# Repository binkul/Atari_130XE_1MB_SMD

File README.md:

# This Atari 130 XE motherboard with 1MB SIMM expansion, internal 
- Atari Basic
- Basic XL
- Basic XE
- Action!
- Mac65
- TTP
# in SMD version

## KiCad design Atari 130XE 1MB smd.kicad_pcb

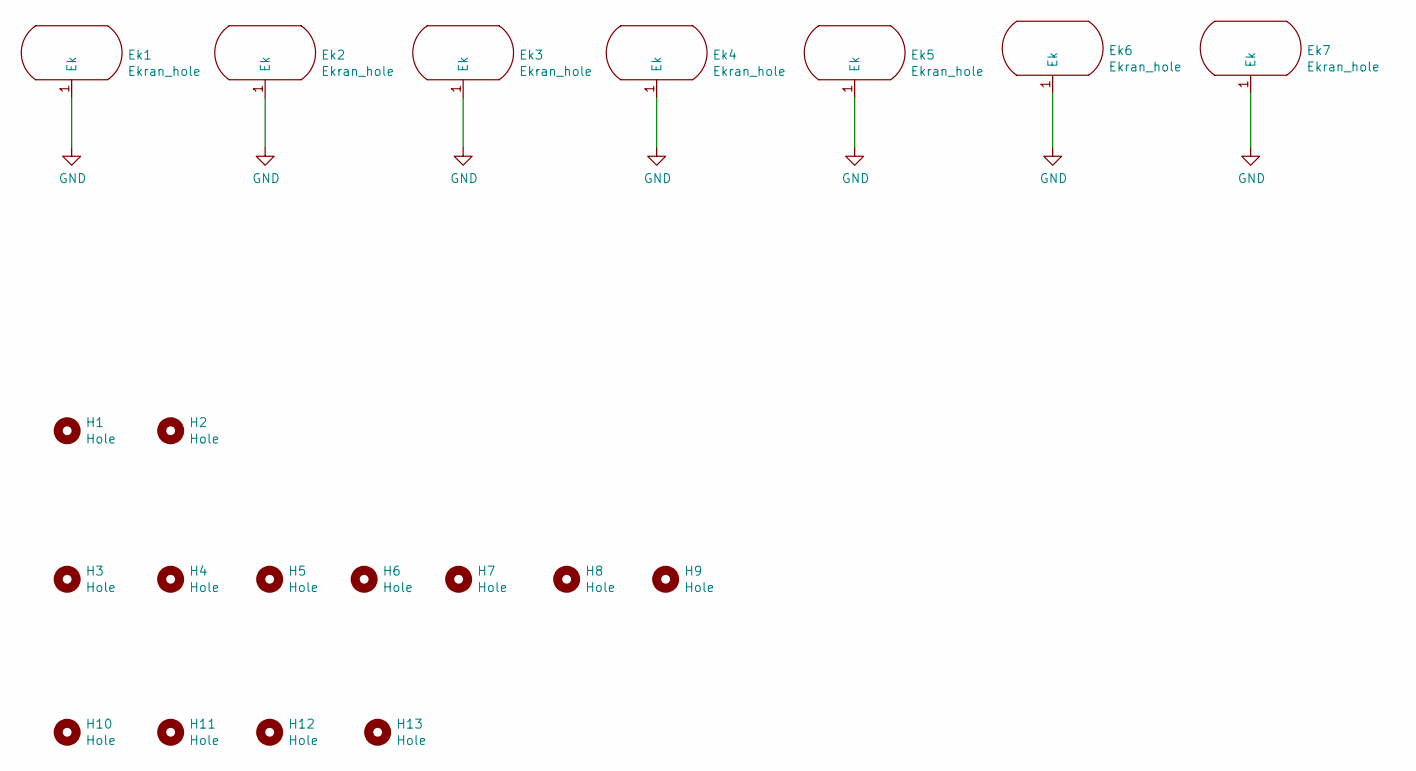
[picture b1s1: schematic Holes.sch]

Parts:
Ek1, Ek2, Ek3, Ek4, Ek5, Ek6, Ek7: Ekran_hole; Ekran_GND
H1, H2: Hole; Medium_hole
H3, H4, H5, H6, H7, H8, H9: Hole; Hole_3.4mm
H10, H11, H12, H13: Hole; Hole_4.4mm

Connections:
GND: Ek1.1, Ek2.1, Ek3.1, Ek4.1, Ek5.1, Ek6.1, Ek7.1; also elsewhere on the board

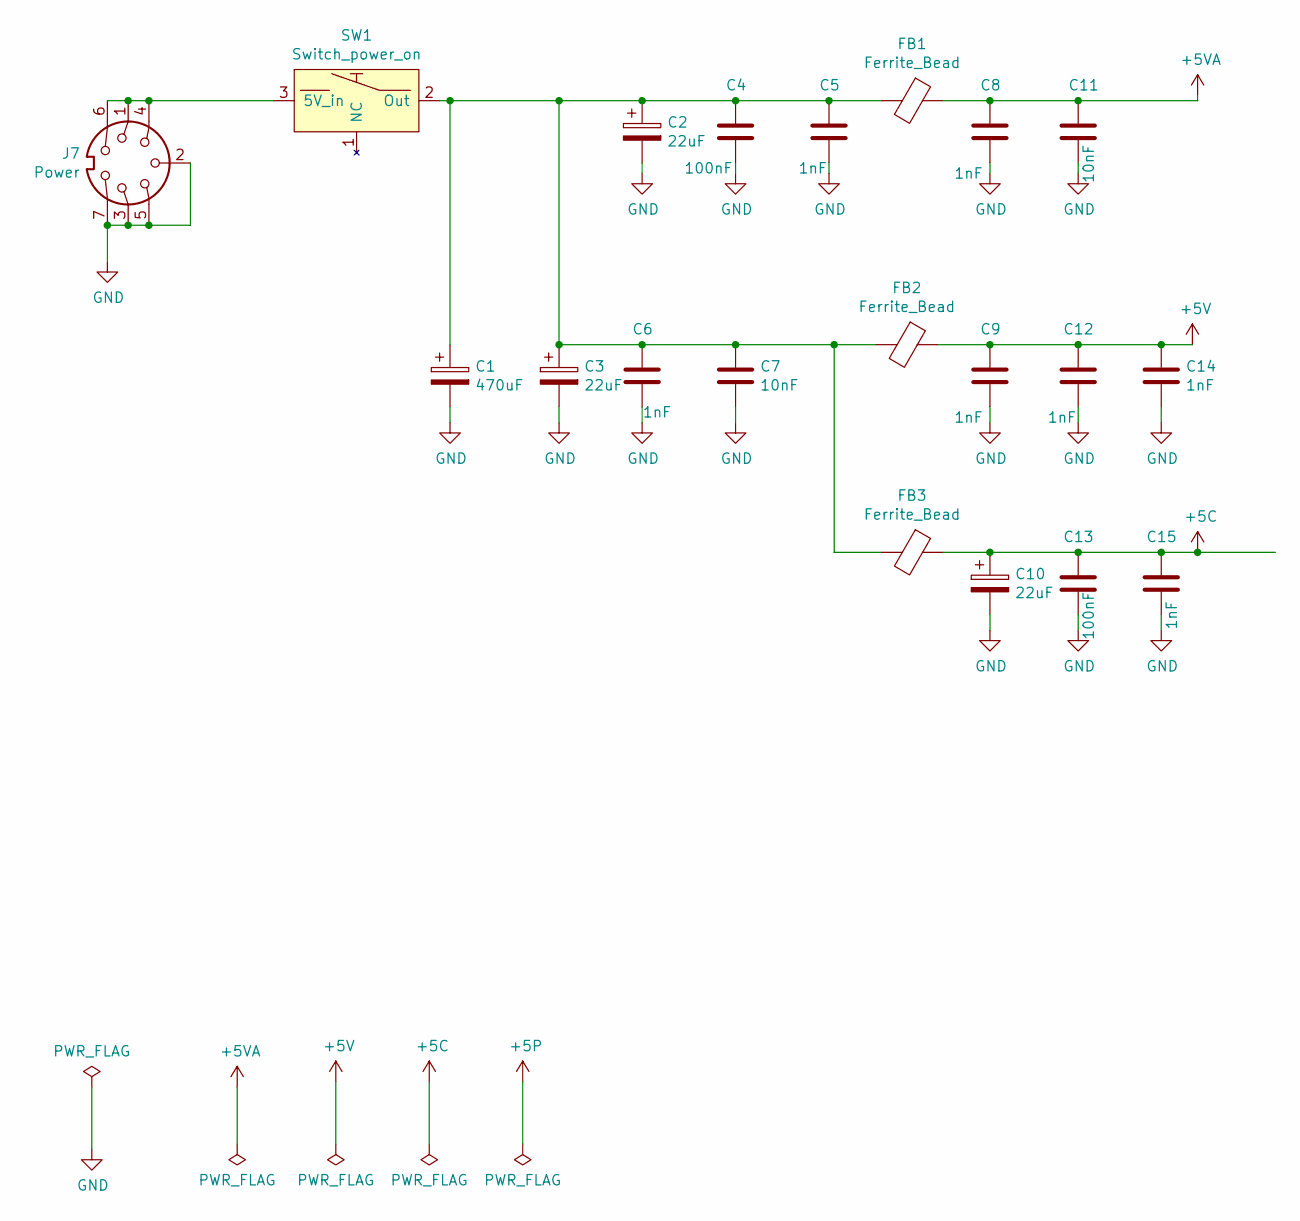
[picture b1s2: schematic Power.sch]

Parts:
C1: 470uF; CP_Elec_10x10.5
C2, C3, C10: 22uF; CP_Elec_6.3x5.2
C4, C13: 100nF; C_1206_3216Metric_Pad1.42x1.75mm_HandSolder
C5, C6, C8, C9, C12, C14, C15: 1nF; C_1206_3216Metric_Pad1.42x1.75mm_HandSolder
C7, C11: 10nF; C_1206_3216Metric_Pad1.42x1.75mm_HandSolder
FB1, FB2, FB3: Ferrite_Bead; L_1812_4532Metric_Pad1.30x3.40mm_HandSolder
J7: Power; DIN_7_pin
SW1: Switch_power_on; Switch_ON-OFF

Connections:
+5C: C10.1, C13.1, C15.1, FB3.1; also elsewhere on the board
+5V: C9.1, C12.1, C14.1, FB2.1
+5VA: C8.1, C11.1, FB1.1; also elsewhere on the board
GND: C1.2, C2.2, C3.2, C4.2, C5.2, C6.2, C7.2, C8.2, C9.2, C10.2, C11.2, C12.2, C13.2, C14.2, C15.2, J7.2, J7.3, J7.5, J7.7; also elsewhere on the board
unnamed: C1.1, C2.1, C3.1, C4.1, C5.1, C6.1, C7.1, FB1.2, FB2.2, FB3.2, SW1.2 (Out)
unnamed: J7.1, J7.4, J7.6, SW1.3 (5V_in)

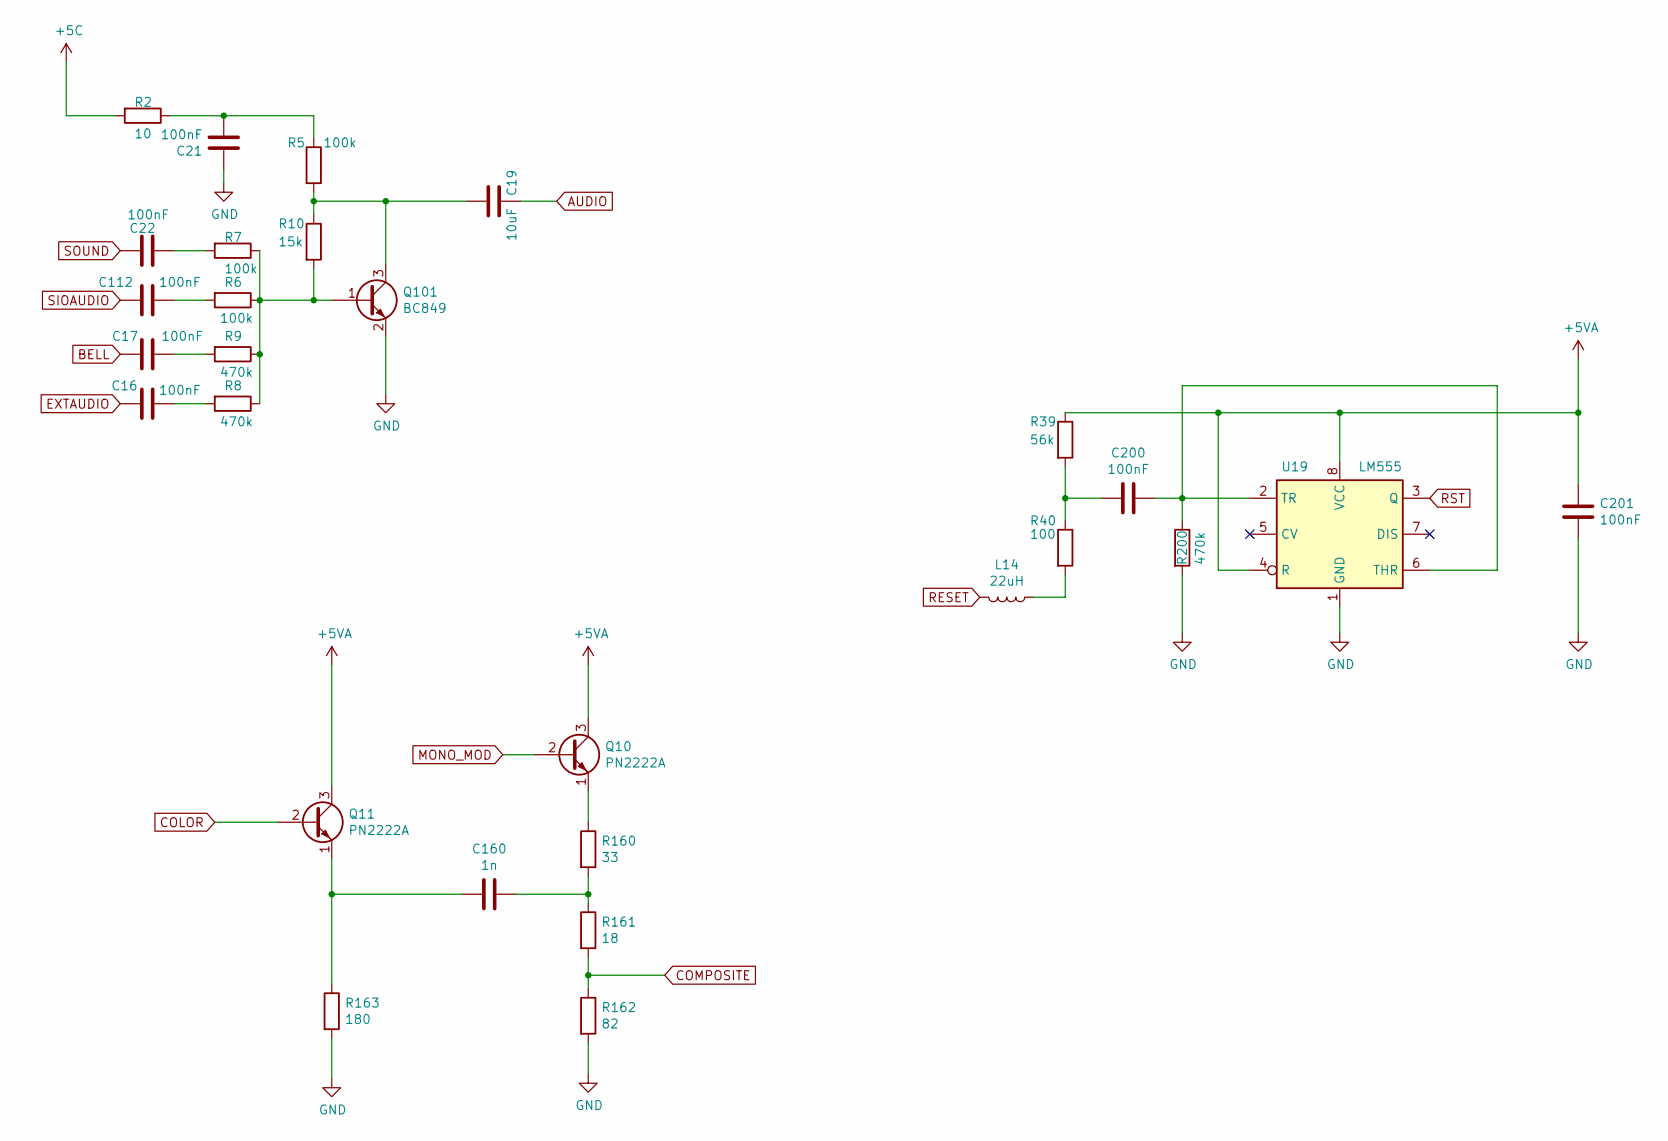
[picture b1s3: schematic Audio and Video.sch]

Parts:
C16, C17, C21, C22, C112, C200, C201: 100nF; C_1206_3216Metric_Pad1.42x1.75mm_HandSolder
C19: 10uF; C_1210_3225Metric_Pad1.42x2.65mm_HandSolder
C160: 1n; C_1206_3216Metric_Pad1.42x1.75mm_HandSolder
L14: 22uH; L_1812_4532Metric_Pad1.30x3.40mm_HandSolder
Q10, Q11: PN2222A; TO-92_Inline
Q101: BC849; SOT-23
R2: 10; R_1206_3216Metric_Pad1.42x1.75mm_HandSolder
R5, R6, R7: 100k; R_1206_3216Metric_Pad1.42x1.75mm_HandSolder
R8, R9, R200: 470k; R_1206_3216Metric_Pad1.42x1.75mm_HandSolder
R10: 15k; R_1206_3216Metric_Pad1.42x1.75mm_HandSolder
R39: 56k; R_1206_3216Metric_Pad1.42x1.75mm_HandSolder
R40: 100; R_1206_3216Metric_Pad1.42x1.75mm_HandSolder
R160: 33; R_1206_3216Metric_Pad1.42x1.75mm_HandSolder
R161: 18; R_1206_3216Metric_Pad1.42x1.75mm_HandSolder
R162: 82; R_1206_3216Metric_Pad1.42x1.75mm_HandSolder
R163: 180; R_1206_3216Metric_Pad1.42x1.75mm_HandSolder
U19: LM555; DIP-8_W7.62mm_Socket

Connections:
+5C: R2.2; also elsewhere on the board
+5VA: C201.1, Q10.3 (C), Q11.3 (C), R39.1, U19.4 (R), U19.8 (VCC); also elsewhere on the board
AUDIO: C19.2; also elsewhere on the board
BELL: C17.2; also elsewhere on the board
COLOR: Q11.2 (B); also elsewhere on the board
COMPOSITE: R161.2, R162.1; also elsewhere on the board
EXTAUDIO: C16.1; also elsewhere on the board
GND: C21.1, C201.2, Q101.2 (E), R162.2, R163.2, R200.2, U19.1 (GND); also elsewhere on the board
MONO_MOD: Q10.2 (B); also elsewhere on the board
unnamed: C16.2, R8.2
unnamed: C17.1, R9.2
unnamed: C19.1, Q101.3 (C), R5.2, R10.1
unnamed: C21.2, R2.1, R5.1
unnamed: C22.2, R7.2
unnamed: C112.2, R6.2
unnamed: C160.1, R160.2, R161.1
unnamed: C160.2, Q11.1 (E), R163.1
unnamed: C200.1, R200.1, U19.2 (TR), U19.6 (THR)
unnamed: C200.2, R39.2, R40.1
unnamed: L14.1, R40.2
unnamed: Q10.1 (E), R160.1
unnamed: Q101.1 (B), R6.1, R7.1, R8.1, R9.1, R10.2
RESET: L14.2; also elsewhere on the board
RST: U19.3 (Q); also elsewhere on the board
SIOAUDIO: C112.1; also elsewhere on the board
SOUND: C22.1; also elsewhere on the board

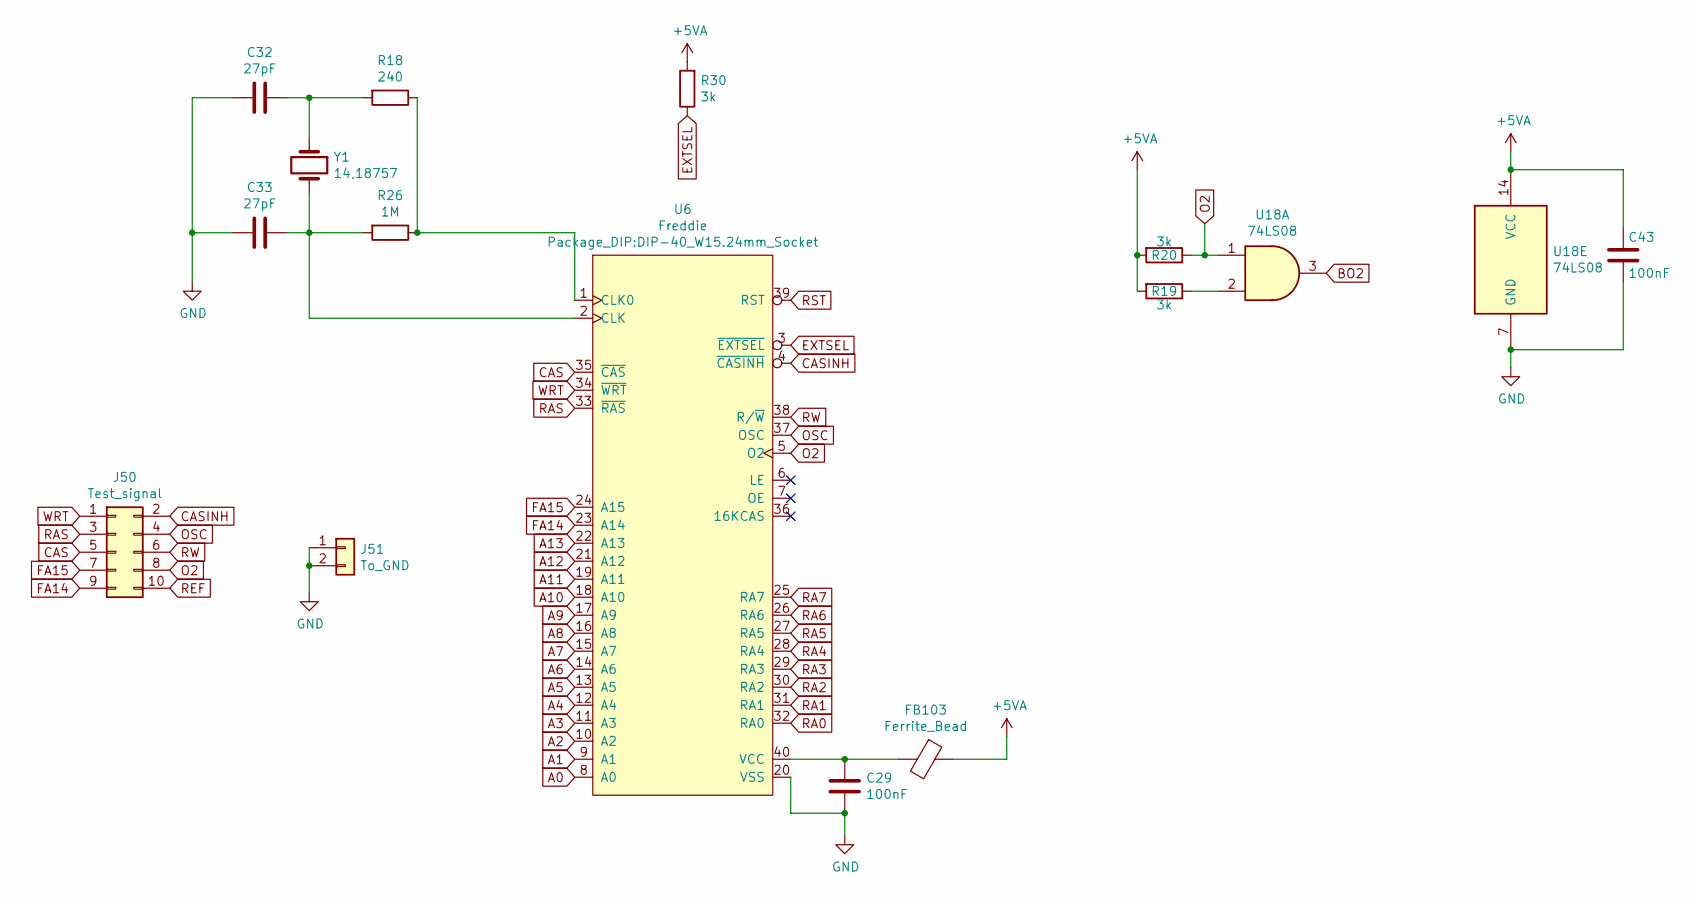
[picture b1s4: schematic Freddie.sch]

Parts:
C29, C43: 100nF; C_1206_3216Metric_Pad1.42x1.75mm_HandSolder
C32, C33: 27pF; C_1206_3216Metric_Pad1.42x1.75mm_HandSolder
FB103: Ferrite_Bead; L_1812_4532Metric_Pad1.30x3.40mm_HandSolder
J50: Test_signal; PinHeader_2x05_P2.54mm_Vertical
J51: To_GND; PinHeader_1x02_P2.54mm_Vertical
R18: 240; R_1206_3216Metric_Pad1.42x1.75mm_HandSolder
R19, R20, R30: 3k; R_1206_3216Metric_Pad1.42x1.75mm_HandSolder
R26: 1M; R_1206_3216Metric_Pad1.42x1.75mm_HandSolder
U6: Freddie; DIP-40_W15.24mm_Socket
U18: 74LS08; DIP-14_W7.62mm_Socket
Y1: 14,18757; Crystal_HC18-U_Vertical

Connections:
+5VA: C43.1, FB103.1, R19.2, R20.2, R30.2, U18.14 (VCC); also elsewhere on the board
A0: U6.8 (A0); also elsewhere on the board
A1: U6.9 (A1); also elsewhere on the board
A2: U6.10 (A2); also elsewhere on the board
A3: U6.11 (A3); also elsewhere on the board
A4: U6.12 (A4); also elsewhere on the board
A5: U6.13 (A5); also elsewhere on the board
A6: U6.14 (A6); also elsewhere on the board
A7: U6.15 (A7); also elsewhere on the board
A8: U6.16 (A8); also elsewhere on the board
A9: U6.17 (A9); also elsewhere on the board
A10: U6.18 (A10); also elsewhere on the board
A11: U6.19 (A11); also elsewhere on the board
A12: U6.21 (A12); also elsewhere on the board
A13: U6.22 (A13); also elsewhere on the board
BO2: U18.3; also elsewhere on the board
CAS: J50.5, U6.35 (~CAS); also elsewhere on the board
CASINH: J50.2, U6.4 (~CASINH); also elsewhere on the board
EXTSEL: R30.1, U6.3 (~EXTSEL); also elsewhere on the board
FA14: J50.9, U6.23 (A14); also elsewhere on the board
FA15: J50.7, U6.24 (A15); also elsewhere on the board
GND: C29.2, C32.2, C33.2, C43.2, J51.1, J51.2, U6.20 (VSS), U18.7 (GND); also elsewhere on the board
unnamed: C29.1, FB103.2, U6.40 (VCC)
unnamed: C32.1, R18.2, Y1.1
unnamed: C33.1, R26.2, U6.2 (CLK), Y1.2
unnamed: R18.1, R26.1, U6.1 (CLK0)
unnamed: R19.1, U18.2
O2: J50.8, R20.1, U6.5 (O2), U18.1; also elsewhere on the board
OSC: J50.4, U6.37 (OSC); also elsewhere on the board
RA0: U6.32 (RA0); also elsewhere on the board
RA1: U6.31 (RA1); also elsewhere on the board
RA2: U6.30 (RA2); also elsewhere on the board
RA3: U6.29 (RA3); also elsewhere on the board
RA4: U6.28 (RA4); also elsewhere on the board
RA5: U6.27 (RA5); also elsewhere on the board
RA6: U6.26 (RA6); also elsewhere on the board
RA7: U6.25 (RA7); also elsewhere on the board
RAS: J50.3, U6.33 (~RAS); also elsewhere on the board
REF: J50.10; also elsewhere on the board
RST: U6.39 (RST); also elsewhere on the board
RW: J50.6, U6.38 (R/~W); also elsewhere on the board
WRT: J50.1, U6.34 (~WRT); also elsewhere on the board

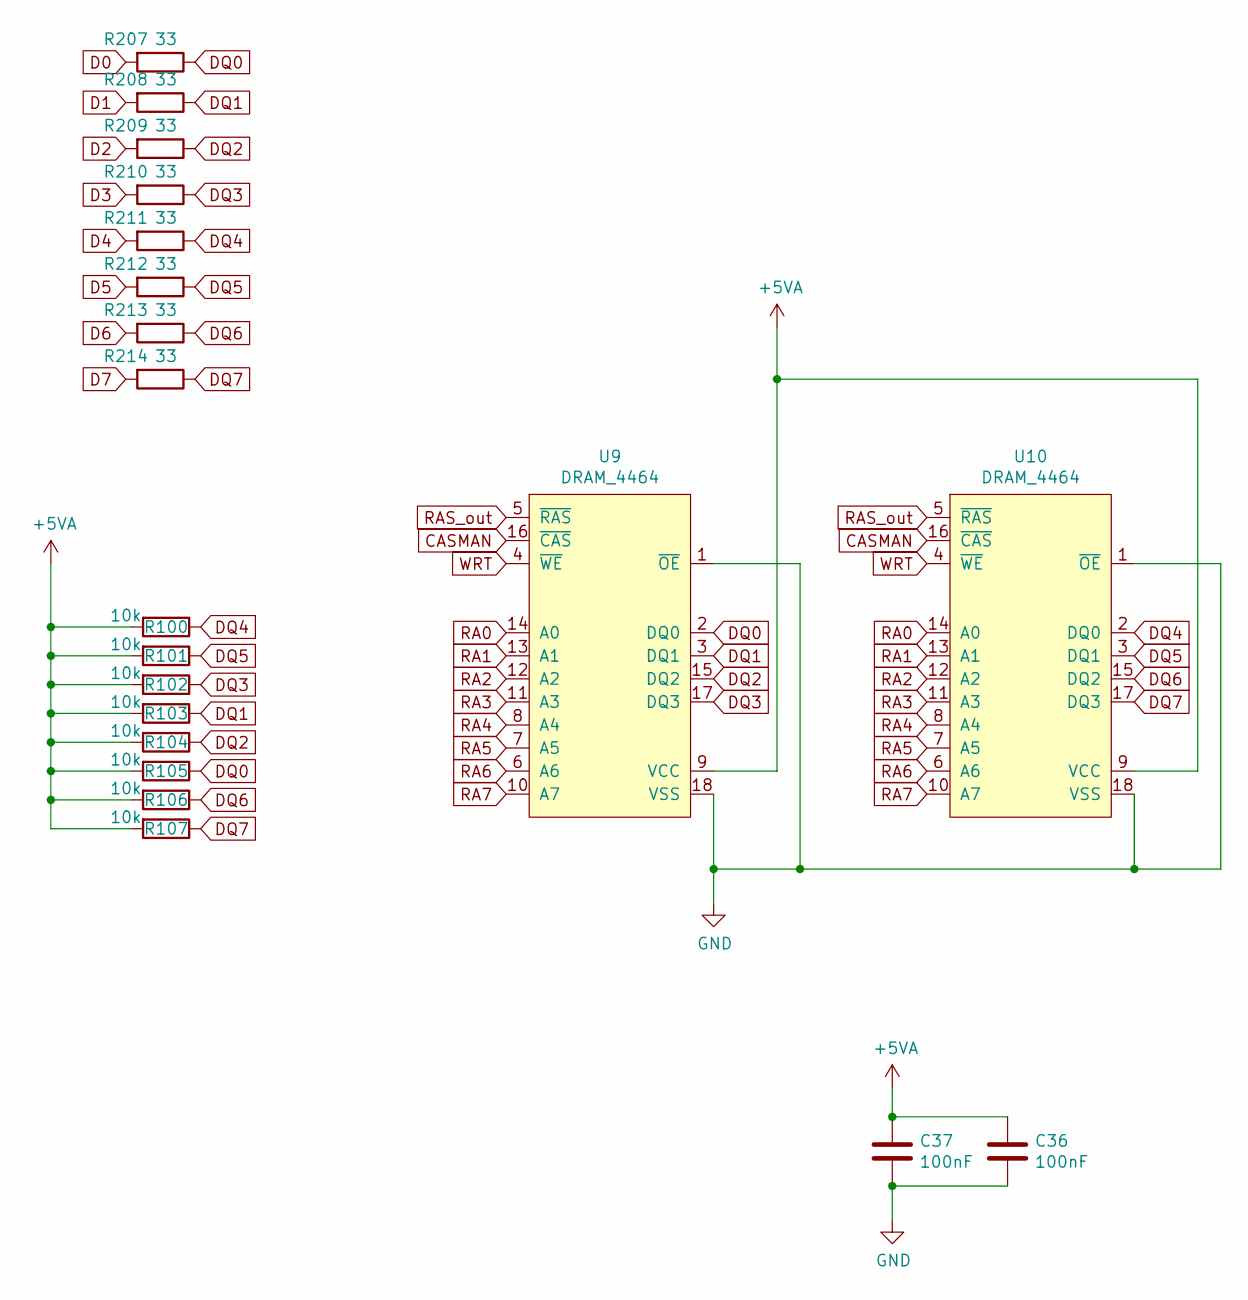
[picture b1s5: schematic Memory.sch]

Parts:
C36, C37: 100nF; C_Axial_L3.8mm_D2.6mm_P7.50mm_Horizontal
R100, R101, R102, R103, R104, R105, R106, R107: 10k; R_1206_3216Metric_Pad1.42x1.75mm_HandSolder
R207, R208, R209, R210, R211, R212, R213, R214: 33; R_1206_3216Metric_Pad1.42x1.75mm_HandSolder
U9, U10: DRAM_4464; DIP-18_W7.62mm

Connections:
+5VA: C36.1, C37.1, R100.2, R101.2, R102.2, R103.2, R104.2, R105.2, R106.2, R107.2, U9.9 (VCC), U10.9 (VCC); also elsewhere on the board
CASMAN: U9.16 (~CAS), U10.16 (~CAS); also elsewhere on the board
D0: R207.2; also elsewhere on the board
D1: R208.2; also elsewhere on the board
D2: R209.2; also elsewhere on the board
D3: R210.2; also elsewhere on the board
D4: R211.2; also elsewhere on the board
D5: R212.2; also elsewhere on the board
D6: R213.2; also elsewhere on the board
D7: R214.2; also elsewhere on the board
DQ0: R105.1, R207.1, U9.2 (DQ0); also elsewhere on the board
DQ1: R103.1, R208.1, U9.3 (DQ1); also elsewhere on the board
DQ2: R104.1, R209.1, U9.15 (DQ2); also elsewhere on the board
DQ3: R102.1, R210.1, U9.17 (DQ3); also elsewhere on the board
DQ4: R100.1, R211.1, U10.2 (DQ0); also elsewhere on the board
DQ5: R101.1, R212.1, U10.3 (DQ1); also elsewhere on the board
DQ6: R106.1, R213.1, U10.15 (DQ2); also elsewhere on the board
DQ7: R107.1, R214.1, U10.17 (DQ3); also elsewhere on the board
GND: C36.2, C37.2, U9.1 (~OE), U9.18 (VSS), U10.1 (~OE), U10.18 (VSS); also elsewhere on the board
RA0: U9.14 (A0), U10.14 (A0); also elsewhere on the board
RA1: U9.13 (A1), U10.13 (A1); also elsewhere on the board
RA2: U9.12 (A2), U10.12 (A2); also elsewhere on the board
RA3: U9.11 (A3), U10.11 (A3); also elsewhere on the board
RA4: U9.8 (A4), U10.8 (A4); also elsewhere on the board
RA5: U9.7 (A5), U10.7 (A5); also elsewhere on the board
RA6: U9.6 (A6), U10.6 (A6); also elsewhere on the board
RA7: U9.10 (A7), U10.10 (A7); also elsewhere on the board
RAS_out: U9.5 (~RAS), U10.5 (~RAS); also elsewhere on the board
WRT: U9.4 (~WE), U10.4 (~WE); also elsewhere on the board

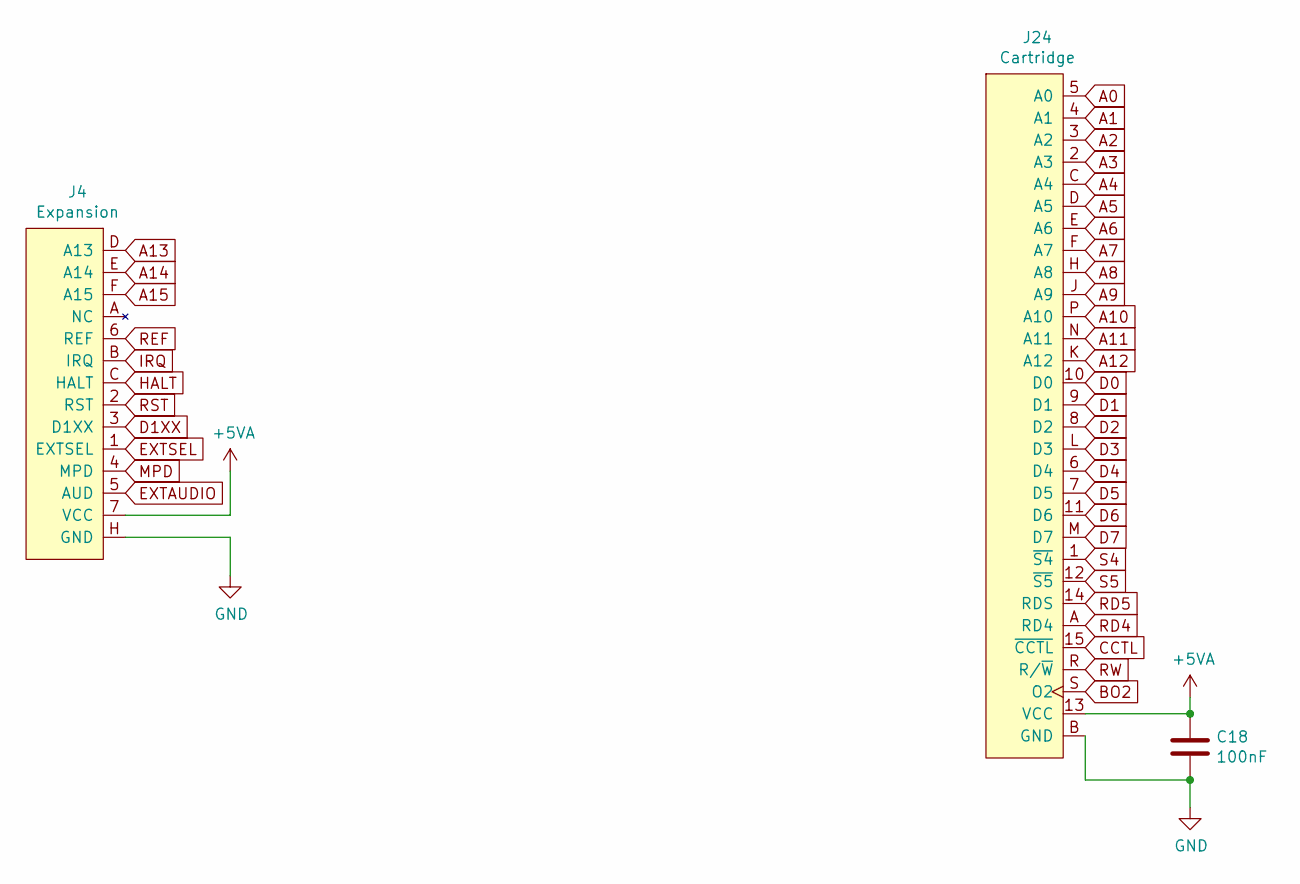
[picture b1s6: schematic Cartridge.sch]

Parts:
C18: 100nF; C_1206_3216Metric_Pad1.42x1.75mm_HandSolder
J4: Expansion; Expansion_Slot
J24: Cartridge; Cartridge_Slot

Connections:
+5VA: C18.1, J4.7 (VCC), J24.13 (VCC); also elsewhere on the board
A0: J24.5 (A0); also elsewhere on the board
A1: J24.4 (A1); also elsewhere on the board
A2: J24.3 (A2); also elsewhere on the board
A3: J24.2 (A3); also elsewhere on the board
A4: J24.C (A4); also elsewhere on the board
A5: J24.D (A5); also elsewhere on the board
A6: J24.E (A6); also elsewhere on the board
A7: J24.F (A7); also elsewhere on the board
A8: J24.H (A8); also elsewhere on the board
A9: J24.J (A9); also elsewhere on the board
A10: J24.P (A10); also elsewhere on the board
A11: J24.N (A11); also elsewhere on the board
A12: J24.K (A12); also elsewhere on the board
A13: J4.D (A13); also elsewhere on the board
A14: J4.E (A14); also elsewhere on the board
A15: J4.F (A15); also elsewhere on the board
BO2: J24.S (O2); also elsewhere on the board
CCTL: J24.15 (~CCTL); also elsewhere on the board
D0: J24.10 (D0); also elsewhere on the board
D1: J24.9 (D1); also elsewhere on the board
D1XX: J4.3 (D1XX); also elsewhere on the board
D2: J24.8 (D2); also elsewhere on the board
D3: J24.L (D3); also elsewhere on the board
D4: J24.6 (D4); also elsewhere on the board
D5: J24.7 (D5); also elsewhere on the board
D6: J24.11 (D6); also elsewhere on the board
D7: J24.M (D7); also elsewhere on the board
EXTAUDIO: J4.5 (AUD); also elsewhere on the board
EXTSEL: J4.1 (EXTSEL); also elsewhere on the board
GND: C18.2, J4.H (GND), J24.B (GND); also elsewhere on the board
HALT: J4.C (HALT); also elsewhere on the board
IRQ: J4.B (IRQ); also elsewhere on the board
MPD: J4.4 (MPD); also elsewhere on the board
RD4: J24.A (RD4); also elsewhere on the board
RD5: J24.14 (RDS); also elsewhere on the board
REF: J4.6 (REF); also elsewhere on the board
RST: J4.2 (RST); also elsewhere on the board
RW: J24.R (R/~W); also elsewhere on the board
S4: J24.1 (~S4); also elsewhere on the board
S5: J24.12 (~S5); also elsewhere on the board

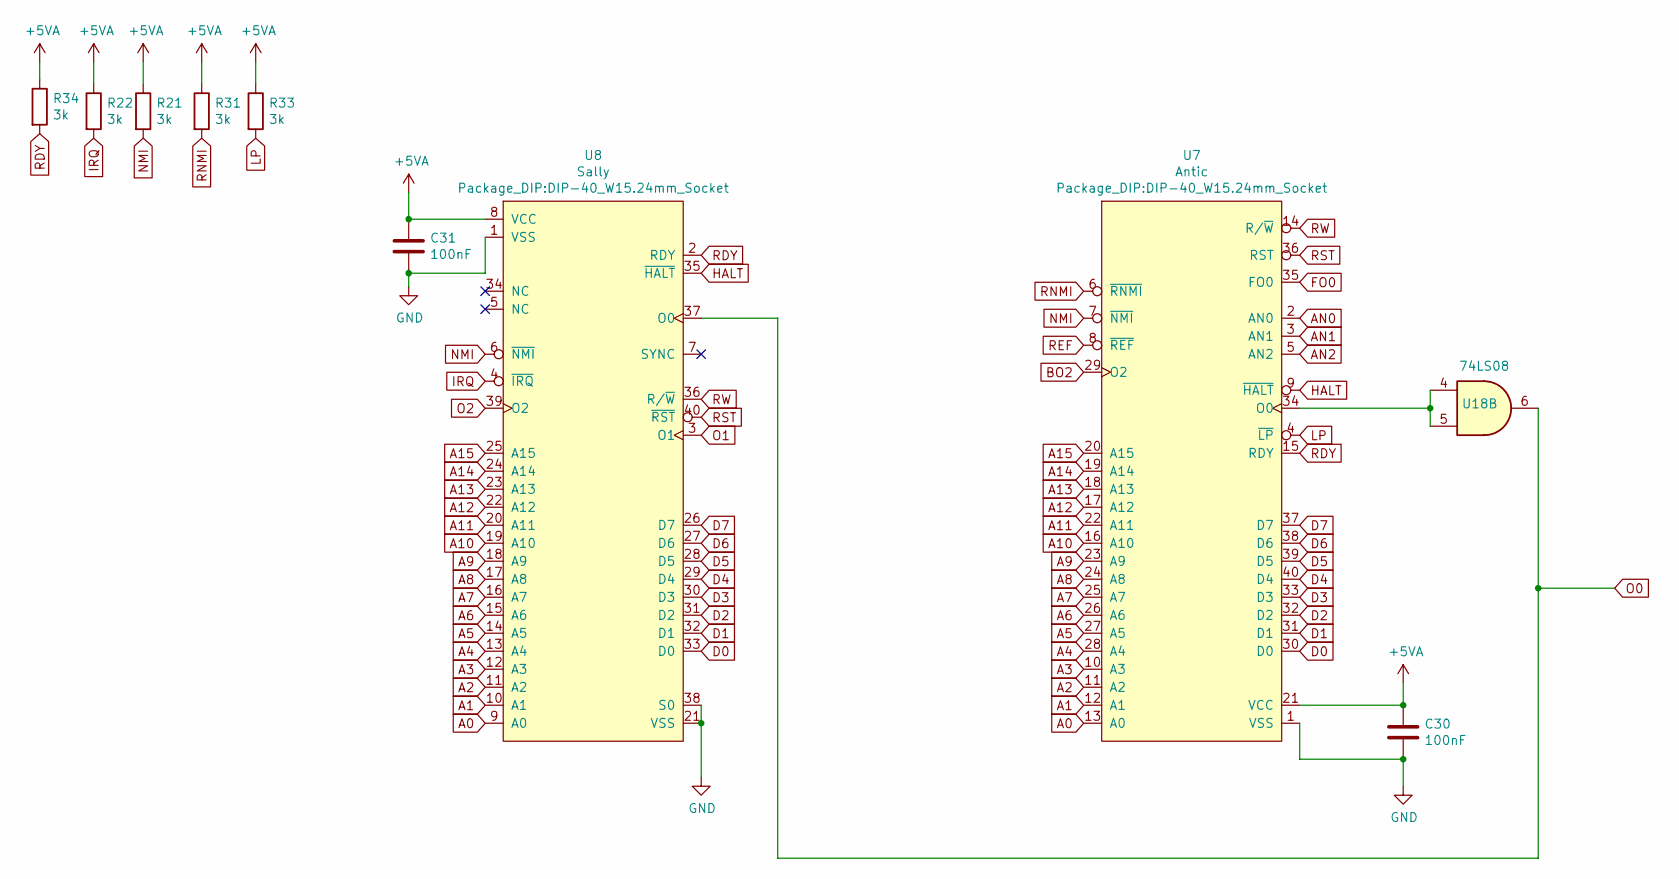
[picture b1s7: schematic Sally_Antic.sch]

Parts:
C30, C31: 100nF; C_1206_3216Metric_Pad1.42x1.75mm_HandSolder
R21, R22, R31, R33, R34: 3k; R_1206_3216Metric_Pad1.42x1.75mm_HandSolder
U7: Antic; DIP-40_W15.24mm_Socket
U8: Sally; DIP-40_W15.24mm_Socket
U18: 74LS08; DIP-14_W7.62mm_Socket

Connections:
+5VA: C30.1, C31.1, R21.1, R22.1, R31.1, R33.1, R34.1, U7.21 (VCC), U8.8 (VCC); also elsewhere on the board
A0: U7.13 (A0), U8.9 (A0); also elsewhere on the board
A1: U7.12 (A1), U8.10 (A1); also elsewhere on the board
A2: U7.11 (A2), U8.11 (A2); also elsewhere on the board
A3: U7.10 (A3), U8.12 (A3); also elsewhere on the board
A4: U7.28 (A4), U8.13 (A4); also elsewhere on the board
A5: U7.27 (A5), U8.14 (A5); also elsewhere on the board
A6: U7.26 (A6), U8.15 (A6); also elsewhere on the board
A7: U7.25 (A7), U8.16 (A7); also elsewhere on the board
A8: U7.24 (A8), U8.17 (A8); also elsewhere on the board
A9: U7.23 (A9), U8.18 (A9); also elsewhere on the board
A10: U7.16 (A10), U8.19 (A10); also elsewhere on the board
A11: U7.22 (A11), U8.20 (A11); also elsewhere on the board
A12: U7.17 (A12), U8.22 (A12); also elsewhere on the board
A13: U7.18 (A13), U8.23 (A13); also elsewhere on the board
A14: U7.19 (A14), U8.24 (A14); also elsewhere on the board
A15: U7.20 (A15), U8.25 (A15); also elsewhere on the board
AN0: U7.2 (AN0); also elsewhere on the board
AN1: U7.3 (AN1); also elsewhere on the board
AN2: U7.5 (AN2); also elsewhere on the board
BO2: U7.29 (O2); also elsewhere on the board
D0: U7.30 (D0), U8.33 (D0); also elsewhere on the board
D1: U7.31 (D1), U8.32 (D1); also elsewhere on the board
D2: U7.32 (D2), U8.31 (D2); also elsewhere on the board
D3: U7.33 (D3), U8.30 (D3); also elsewhere on the board
D4: U7.40 (D4), U8.29 (D4); also elsewhere on the board
D5: U7.39 (D5), U8.28 (D5); also elsewhere on the board
D6: U7.38 (D6), U8.27 (D6); also elsewhere on the board
D7: U7.37 (D7), U8.26 (D7); also elsewhere on the board
FO0: U7.35 (FO0); also elsewhere on the board
GND: C30.2, C31.2, U7.1 (VSS), U8.1 (VSS), U8.21 (VSS), U8.38 (S0); also elsewhere on the board
HALT: U7.9 (~HALT), U8.35 (~HALT); also elsewhere on the board
IRQ: R22.2, U8.4 (~IRQ); also elsewhere on the board
LP: R33.2, U7.4 (~LP); also elsewhere on the board
NMI: R21.2, U7.7 (~NMI), U8.6 (~NMI)
unnamed: U7.34 (O0), U18.4, U18.5
O0: U8.37 (O0), U18.6
O1: U8.3 (O1); also elsewhere on the board
O2: U8.39 (O2); also elsewhere on the board
RDY: R34.2, U7.15 (RDY), U8.2 (RDY)
REF: U7.8 (~REF); also elsewhere on the board
RNMI: R31.2, U7.6 (~RNMI)
RST: U7.36 (RST), U8.40 (~RST); also elsewhere on the board
RW: U7.14 (R/~W), U8.36 (R/~W); also elsewhere on the board
